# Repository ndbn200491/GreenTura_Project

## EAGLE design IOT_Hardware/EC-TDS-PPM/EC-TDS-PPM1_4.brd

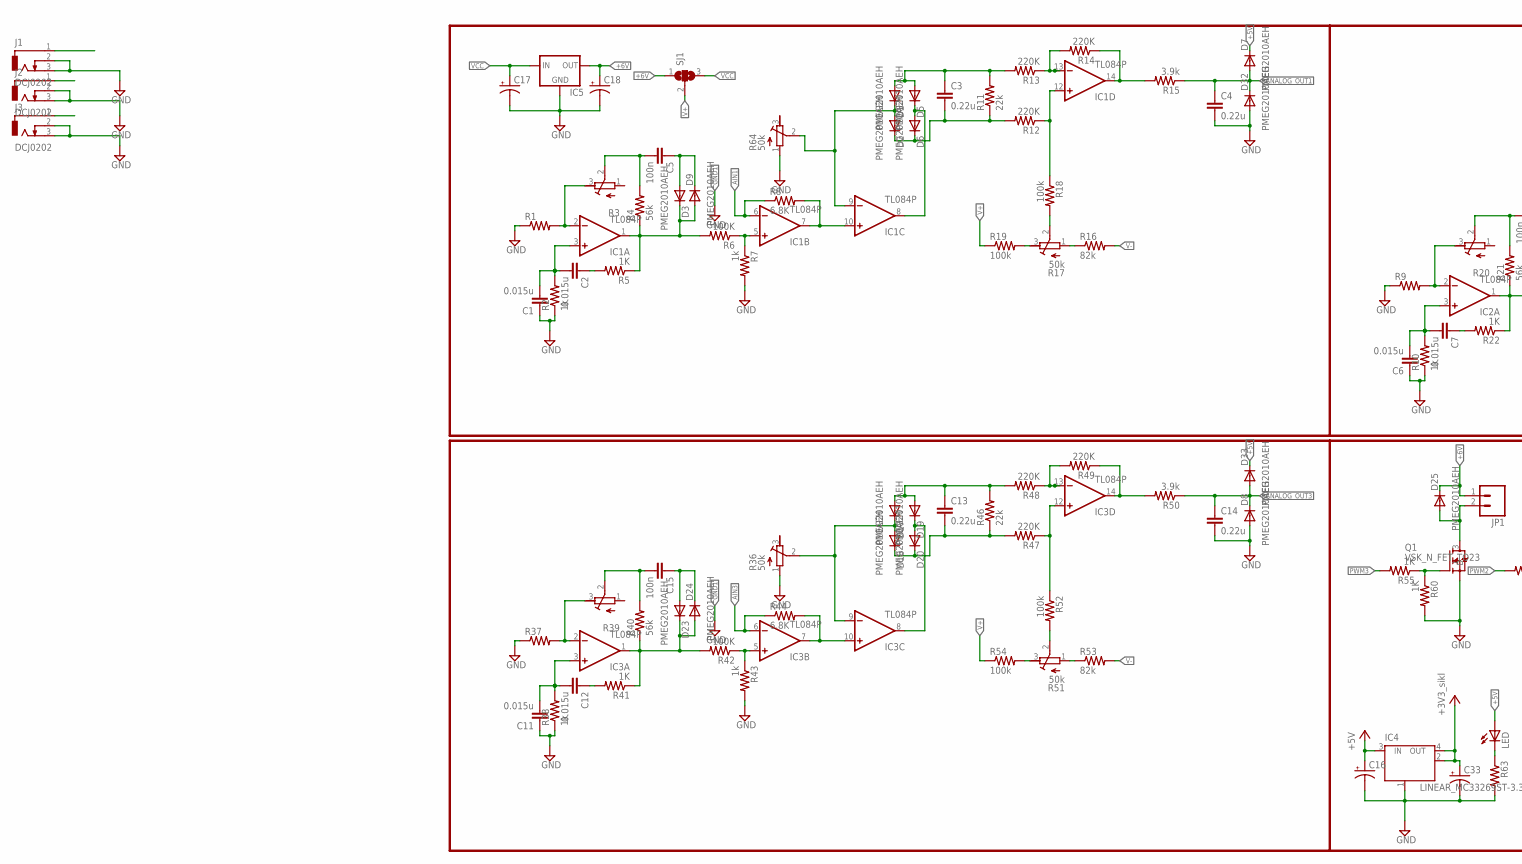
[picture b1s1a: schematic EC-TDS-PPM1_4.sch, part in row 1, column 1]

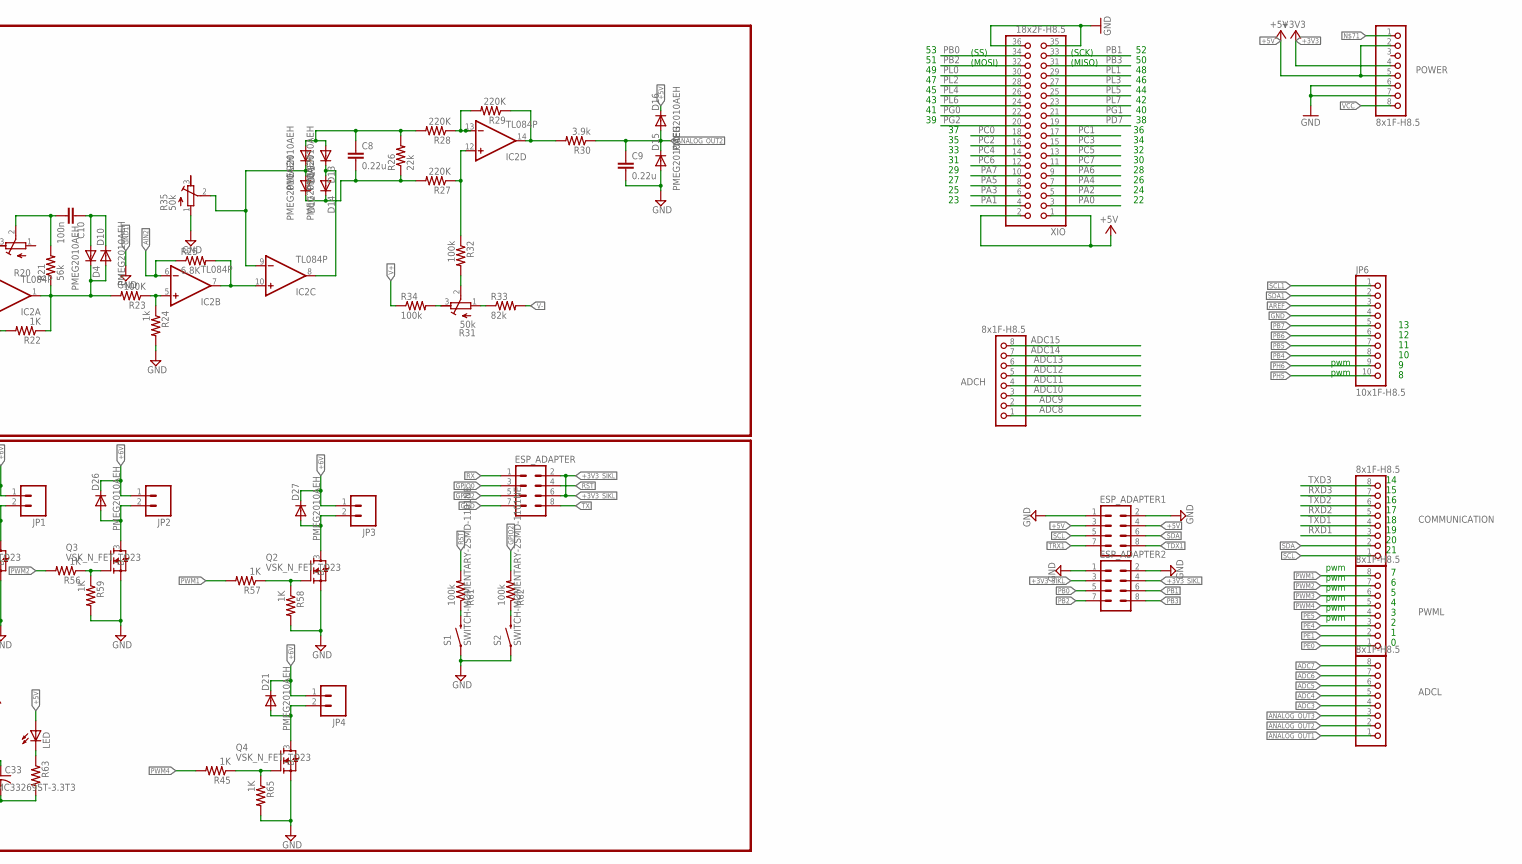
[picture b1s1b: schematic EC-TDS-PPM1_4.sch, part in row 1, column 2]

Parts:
ADCH: 8x1F-H8.5; 1X08
ADCL: 8x1F-H8.5; 1X08
C1, C2, C6, C7, C11, C12: 0.015u; C0603
C3, C4, C8, C9, C13, C14: 0.22u; C0603
C5, C10, C15: 100n; C0603
C16, C17, C18, C33: CPOL-USSMCC; SMC_C
COMMUNICATION: 8x1F-H8.5; 1X08
D1, D2, D3, D4, D5, D6, D7, D8, D9, D10, D11, D12, D13, D14, D15, D16, D17, D18, D19, D20, D21, D23, D24, D25, D26, D27, D32, D33: PMEG2010AEH; SOT123F; PARTNO PMEG2010AEH,115
ESP_ADAPTER, ESP_ADAPTER1, ESP_ADAPTER2: M04X2; 2X4
IC1, IC2, IC3: TL084P; DIL14
IC4: LINEAR_MC33269ST-3.3T3; LINEAR_SOT223
IC5: 78XXS
J1, J2, J3: DCJ0202
JP1, JP2, JP3, JP4: M02PTH; 1X02
JP6: 10x1F-H8.5; 1X10
LED: SPARKFUN_LED0603; SPARKFUN_LED-0603
POWER: 8x1F-H8.5; 1X08
PWML: 8x1F-H8.5; 1X08
Q1, Q2, Q3, Q4: VSK_N_FET_TO23; SOT23
R1, R9, R37: R-US_R0603; R0603
R2, R7, R10, R24, R38, R43: 1k; R0603
R3, R20, R39: R-TRIMM64W; RTRIM64W
R4, R21, R40: 56k; R0603
R5, R22, R41, R45, R55, R56, R57, R58, R59, R60, R65: 1K; R0603
R6, R23, R42: 100K; R0603
R8, R25, R44: 6.8K; R0603
R11, R26, R46: 22k; R0603
R12, R13, R14, R27, R28, R29, R47, R48, R49: 220K; R0603
R15, R30, R50: 3.9k; R0603
R16, R33, R53: 82k; R0603
R17, R31, R35, R36, R51, R64: 50k; RTRIM64W
R18, R19, R32, R34, R52, R54, R61, R62: 100k; R0603
R63: SPARKFUN_RESISTOR0603-RES; SPARKFUN_0603-RES
S1, S2: SWITCH-MOMENTARY-2SMD-1101NE; TACTILE-SWITCH-1101NE
SJ1: SJ2WW; SJ_2W
XIO: 18x2F-H8.5; 2X18

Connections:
+3V3: POWER.4
+3V3_SIKL: C33.+, ESP_ADAPTER.2, ESP_ADAPTER.6, ESP_ADAPTER2.3, ESP_ADAPTER2.4, IC4.2 (OUT), IC4.4 (OUT)
+5V: C16.+, D7.C, D16.C, D33.C, ESP_ADAPTER1.3, ESP_ADAPTER1.4, IC4.3 (IN), LED.A, POWER.2, POWER.5, XIO.1, XIO.2
+6V: C18.+, D21.C, D25.C, D26.C, D27.C, IC5.OUT, JP1.1, JP2.1, JP3.1, JP4.1, SJ1.1
ADC3: ADCL.4
ADC4: ADCL.5
ADC5: ADCL.6
ADC6: ADCL.7
ADC7: ADCL.8
ADC8: ADCH.1
ADC9: ADCH.2
ADC10: ADCH.3
ADC11: ADCH.4
ADC12: ADCH.5
ADC13: ADCH.6
ADC14: ADCH.7
ADC15: ADCH.8
AIN1: IC1.6 (-IN), J1.1, R8.1
AIN2: IC2.6 (-IN), J2.1, R25.1
AIN3: IC3.6 (-IN), J3.1, R44.1
ANALOG_OUT1: ADCL.1, C4.1, D7.A, D32.C, R15.1
ANALOG_OUT2: ADCL.2, C9.1, D15.C, D16.A, R30.1
ANALOG_OUT3: ADCL.3, C14.1, D8.C, D33.A, R50.1
AREF: JP6.3
GND: ESP_ADAPTER.7, JP6.4, POWER.6, POWER.7, XIO.35, XIO.36
GND1: C1.1, C4.2, C6.1, C9.2, C11.1, C14.2, C16.-, C17.-, C18.-, C33.-, D8.A, D15.A, D32.A, ESP_ADAPTER1.1, ESP_ADAPTER1.2, ESP_ADAPTER2.1, ESP_ADAPTER2.2, IC4.1 (GND/ADJ), IC5.GND, J1.2, J1.3, J2.2, J2.3, J3.2, J3.3, Q1.2 (S), Q2.2 (S), Q3.2 (S), Q4.2 (S), R1.1, R2.1, R7.2, R9.1, R10.1, R24.2, R35.1 (A), R36.1 (A), R37.1, R38.1, R43.2, R58.2, R59.2, R60.2, R63.2, R64.1 (A), R65.2, S1.1, S2.1
GPIO0: ESP_ADAPTER.3
GPIO2: ESP_ADAPTER.5, R62.2
unnamed: IC1.2 (-IN), R1.2, R3.3 (E)
unnamed: C2.1, R5.2
unnamed: C1.2, C2.2, IC1.3 (+IN), R2.2
unnamed: IC1.5 (+IN), R6.1, R7.1
unnamed: C5.2, R3.2 (S), R4.2
unnamed: R16.1, R17.1 (A)
unnamed: D3.C, D9.A, IC1.1 (OUT), R4.1, R5.1, R6.2
unnamed: C5.1, D3.A, D9.C
unnamed: IC1.7 (OUT), IC1.10 (+IN), R8.2
unnamed: R17.3 (E), R19.2
unnamed: IC1.13 (-IN), R13.1, R14.2
unnamed: C3.1, D1.A, D5.A, R11.2, R13.2
unnamed: D1.C, D2.A, IC1.9 (-IN), R64.2 (S)
unnamed: C3.2, D2.C, D6.C, R11.1, R12.2
unnamed: D5.C, D6.A, IC1.8 (OUT)
unnamed: IC1.12 (+IN), R12.1, R18.1
unnamed: IC1.14 (OUT), R14.1, R15.2
unnamed: R17.2 (S), R18.2
unnamed: IC2.2 (-IN), R9.2, R20.3 (E)
unnamed: C6.2, C7.2, IC2.3 (+IN), R10.2
unnamed: C10.2, R20.2 (S), R21.2
unnamed: D4.C, D10.A, IC2.1 (OUT), R21.1, R22.1, R23.2
unnamed: C7.1, R22.2
unnamed: IC2.5 (+IN), R23.1, R24.1
unnamed: IC2.7 (OUT), IC2.10 (+IN), R25.2
unnamed: C8.1, D11.A, D13.A, R26.2, R28.2
unnamed: D11.C, D12.A, IC2.9 (-IN), R35.2 (S)
unnamed: C8.2, D12.C, D14.C, R26.1, R27.2
unnamed: D13.C, D14.A, IC2.8 (OUT)
unnamed: IC2.13 (-IN), R28.1, R29.2
unnamed: IC2.12 (+IN), R27.1, R32.1
unnamed: IC2.14 (OUT), R29.1, R30.2
unnamed: C10.1, D4.A, D10.C
unnamed: R31.1 (A), R33.1
unnamed: R31.3 (E), R34.2
unnamed: R31.2 (S), R32.2
unnamed: IC3.2 (-IN), R37.2, R39.3 (E)
unnamed: C11.2, C12.2, IC3.3 (+IN), R38.2
unnamed: C15.2, R39.2 (S), R40.2
unnamed: D23.C, D24.A, IC3.1 (OUT), R40.1, R41.1, R42.2
unnamed: C12.1, R41.2
unnamed: IC3.5 (+IN), R42.1, R43.1
unnamed: IC3.7 (OUT), IC3.10 (+IN), R44.2
unnamed: C13.1, D17.A, D19.A, R46.2, R48.2
unnamed: D17.C, D18.A, IC3.9 (-IN), R36.2 (S)
unnamed: C13.2, D18.C, D20.C, R46.1, R47.2
unnamed: D19.C, D20.A, IC3.8 (OUT)
unnamed: IC3.13 (-IN), R48.1, R49.2
unnamed: IC3.12 (+IN), R47.1, R52.1
unnamed: IC3.14 (OUT), R49.1, R50.2
unnamed: C15.1, D23.A, D24.C
unnamed: R51.1 (A), R53.1
unnamed: R51.3 (E), R54.2
unnamed: R51.2 (S), R52.2
unnamed: D26.A, JP2.2, Q3.3 (D)
unnamed: D27.A, JP3.2, Q2.3 (D)
unnamed: D25.A, JP1.2, Q1.3 (D)
unnamed: Q2.1 (G), R57.1, R58.1
unnamed: Q3.1 (G), R56.1, R59.1
unnamed: D21.A, JP4.2, Q4.3 (D)
unnamed: Q1.1 (G), R55.1, R60.1
unnamed: R61.1, S1.2
unnamed: R62.1, S2.2
unnamed: LED.C, R63.1
unnamed: Q4.1 (G), R45.1, R65.1
PA0: XIO.3
PA1: XIO.4
PA2: XIO.5
PA3: XIO.6
PA4: XIO.7
PA5: XIO.8
PA6: XIO.9
PA7: XIO.10
PB0: ESP_ADAPTER2.5, XIO.34
PB1: ESP_ADAPTER2.6, XIO.33
PB2: ESP_ADAPTER2.7, XIO.32
PB3: ESP_ADAPTER2.8, XIO.31
PB4: JP6.8
PB5: JP6.7
PB6: JP6.6
PB7: JP6.5
PC0: XIO.18
PC1: XIO.17
PC2: XIO.16
PC3: XIO.15
PC4: XIO.14
PC5: XIO.13
PC6: XIO.12
PC7: XIO.11
PD7: XIO.19
PE0: PWML.1
PE1: PWML.2
PE4: PWML.3
PE5: PWML.4
PG0: XIO.22
PG1: XIO.21
PG2: XIO.20
PH5: JP6.10
PH6: JP6.9
PL0: XIO.30
PL1: XIO.29
PL2: XIO.28
PL3: XIO.27
PL4: XIO.26
PL5: XIO.25
PL6: XIO.24
PL7: XIO.23
PWM1: PWML.8, R57.2
PWM2: PWML.7, R56.2
PWM3: PWML.6, R55.2
PWM4: PWML.5, R45.2
RST: ESP_ADAPTER.4, R61.2
RX: ESP_ADAPTER.1
RXD1: COMMUNICATION.3
RXD2: COMMUNICATION.5
RXD3: COMMUNICATION.7
SCL: COMMUNICATION.1, ESP_ADAPTER1.5
SCL1: JP6.1
SDA: COMMUNICATION.2, ESP_ADAPTER1.6
SDA1: JP6.2
TDX1: ESP_ADAPTER1.8
TRX1: ESP_ADAPTER1.7
TX: ESP_ADAPTER.8
TXD1: COMMUNICATION.4
TXD2: COMMUNICATION.6
TXD3: COMMUNICATION.8
V+: IC1.4 (V+), IC2.4 (V+), IC3.4 (V+), R19.1, R34.1, R54.1, SJ1.2
V-: IC1.11 (V-), IC2.11 (V-), IC3.11 (V-), R16.2, R33.2, R53.2
VCC: C17.+, IC5.IN, POWER.8, SJ1.3

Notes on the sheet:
(SS)
(MOSI)
(SCK)
(MISO)
pwm

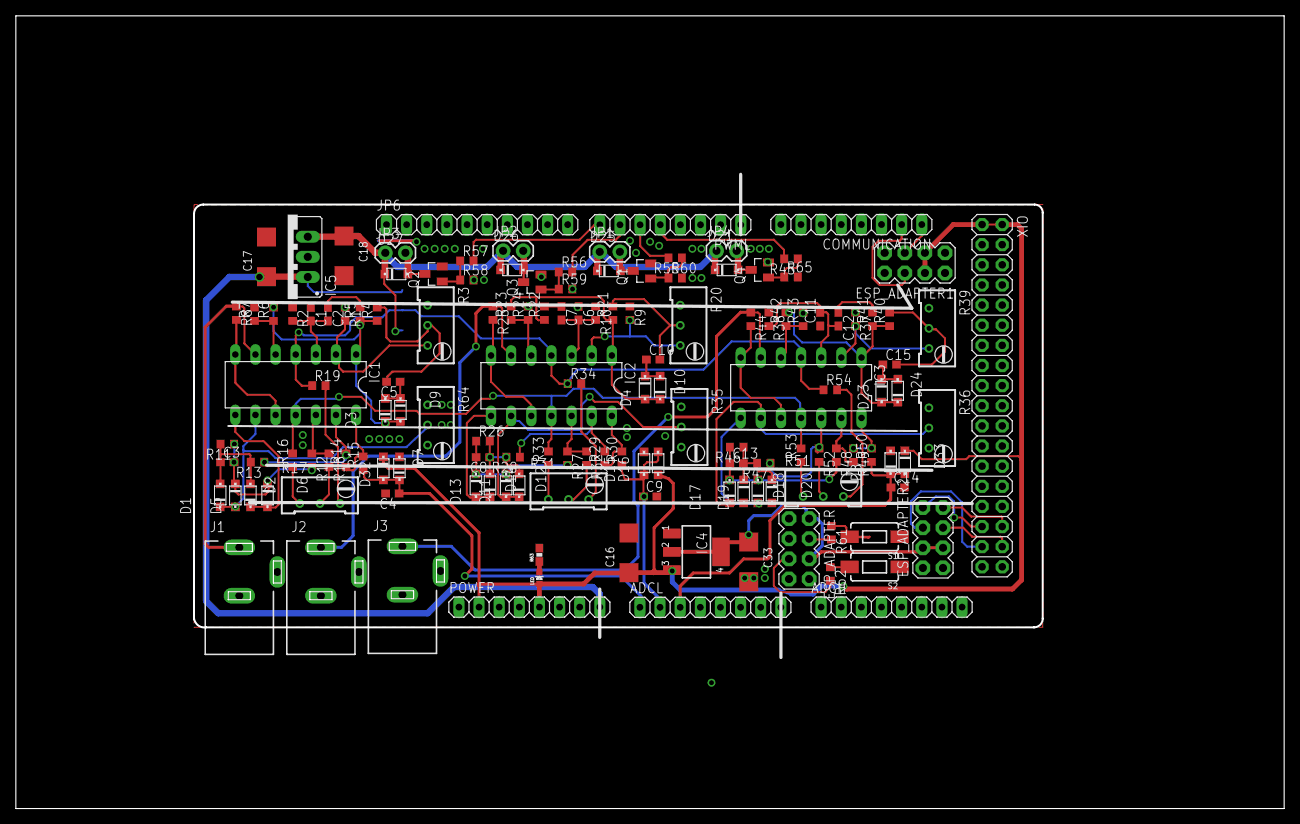
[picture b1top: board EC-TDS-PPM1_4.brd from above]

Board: 2 copper layers, 159.7 x 99.7 mm, 142 parts (1 on the bottom side), 91 nets.

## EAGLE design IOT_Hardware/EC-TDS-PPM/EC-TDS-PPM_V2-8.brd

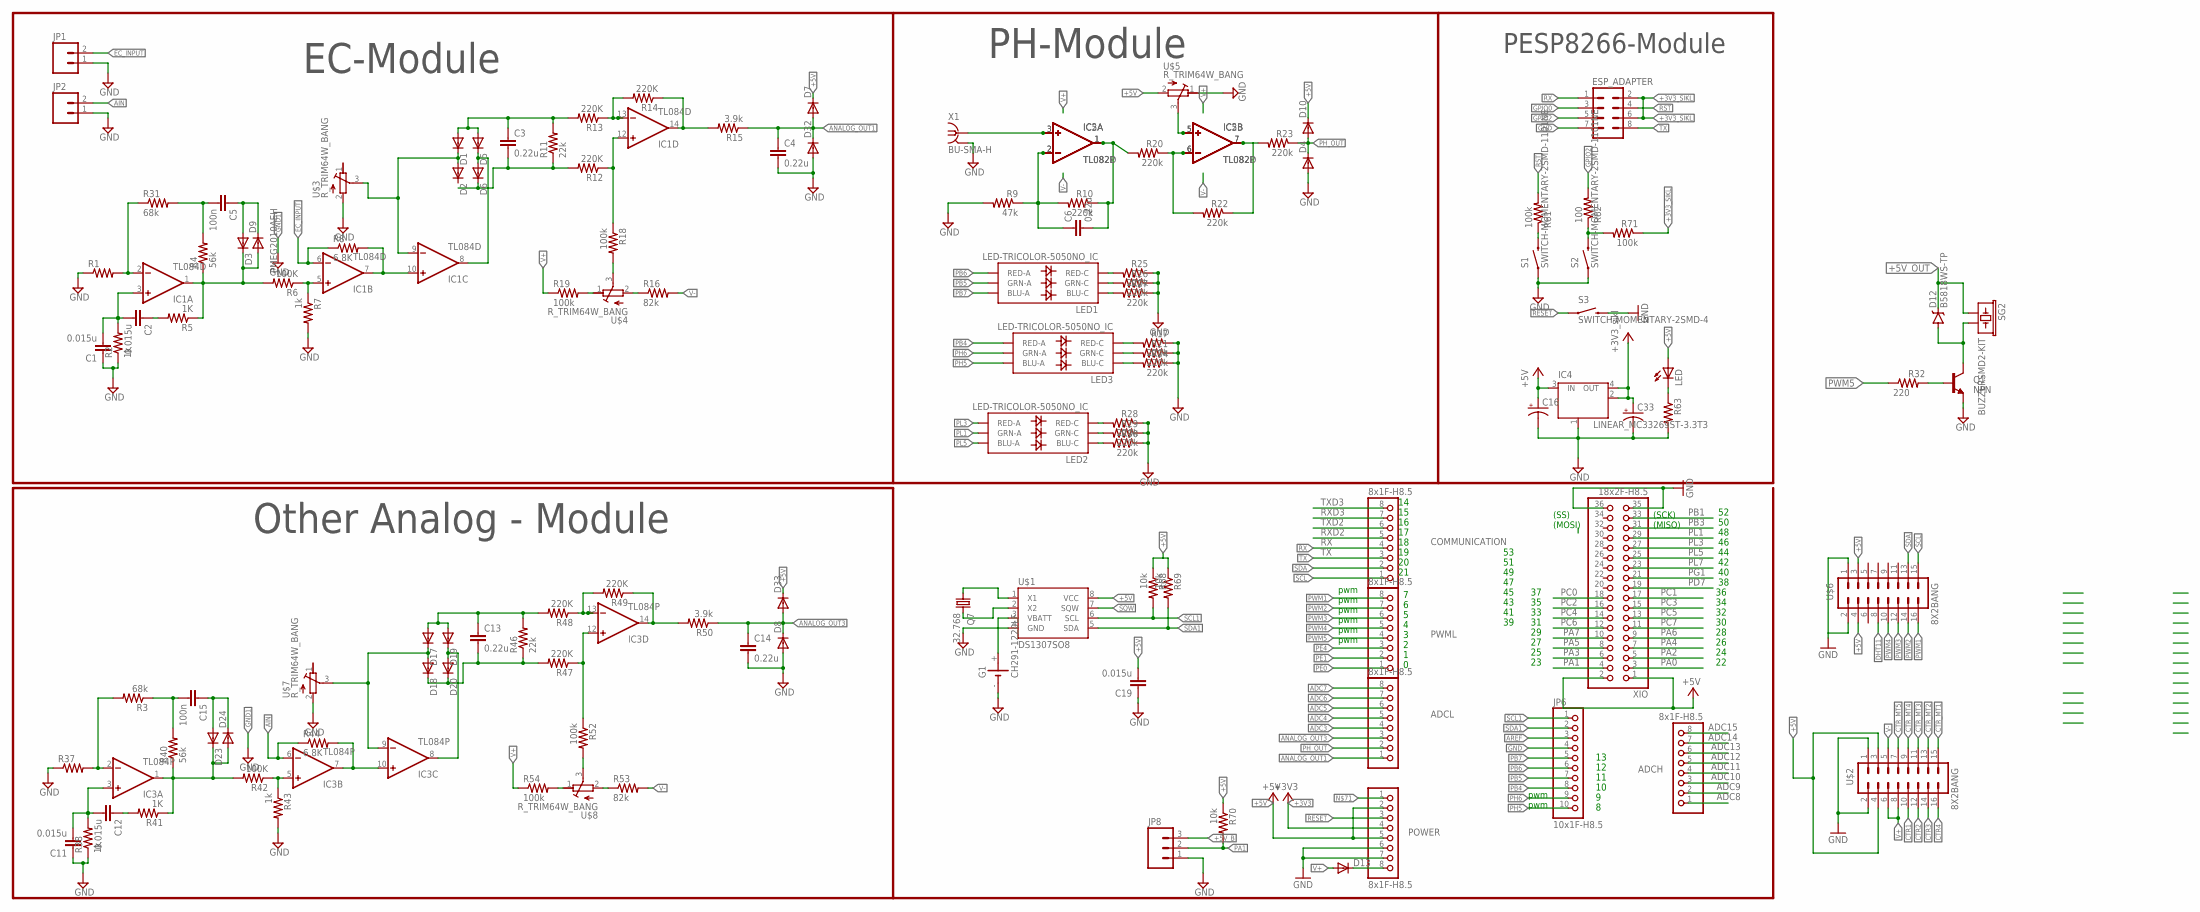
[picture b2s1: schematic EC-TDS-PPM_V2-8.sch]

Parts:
ADCH: 8x1F-H8.5; 1X08
ADCL: 8x1F-H8.5; 1X08
C1, C2, C11, C12, C19: 0.015u; C0603
C3, C4, C6, C13, C14: 0.22u; C0603
C5, C15: 100n; C0603
C16, C33: CPOL-USSMCC; SMC_C
COMMUNICATION: 8x1F-H8.5; 1X08
D1, D2, D3, D4, D5, D6, D7, D8, D9, D10, D13, D17, D18, D19, D20, D23, D24, D32, D33: PMEG2010AEH; SOT123F; PARTNO PMEG2010AEH,115
D12: B5818WS-TP; SOD-323; PARTNO BAT20JFILM
ESP_ADAPTER: M04X2; 2X4
G1: CH291-1220LF
IC1: TL084D; SO14
IC2: TL082P; DIL08
IC3: TL084P; DIL14
IC4: LINEAR_MC33269ST-3.3T3; LINEAR_SOT223
IC5: TL082D; SO08
JP1, JP2: M025MM; SCREWTERMINAL-5MM-2
JP6: 10x1F-H8.5; 1X10
JP8: M03PTH; 1X03
LED: SPARKFUN_LED0603; SPARKFUN_LED-0603
LED1, LED2, LED3: LED-TRICOLOR-5050NO_IC; LED-TRICOLOR-5050
POWER: 8x1F-H8.5; 1X08
PWML: 8x1F-H8.5; 1X08
Q1: NPN; SOT23-3; PARTNO 2SD1048-6-TB-E
Q7: 32.768; TC38H
R1, R37: R-US_R0603; R0603
R2, R7, R38, R43: 1k; R0603
R3, R31: 68k; R0603
R4, R40: 56k; R0603
R5, R41: 1K; R0603
R6, R42: 100K; R0603
R8, R44: 6.8K; R0603
R9: 47k; R0603
R10, R17, R20, R21, R22, R23, R24, R25, R26, R27, R28, R29, R30: 220k; R0603
R11, R46: 22k; R0603
R12, R13, R14, R47, R48, R49: 220K; R0603
R15, R50: 3.9k; R0603
R16, R53: 82k; R0603
R18, R19, R52, R54, R61, R71: 100k; R0603
R32: 220; 0603-RES; PARTNO RT0402DRE079K09L
R62: 100; R0603
R63: SPARKFUN_RESISTOR0603-RES; SPARKFUN_0603-RES
R68, R69, R70: 10k; R0603
S1, S2: SWITCH-MOMENTARY-2SMD-1101NE; TACTILE-SWITCH-1101NE
S3: SWITCH-MOMENTARY-2SMD-4; TACTILE_SWITCH_TALL
SG2: BUZZERSMD2-KIT; BUZZER-CCV-KIT
U$1: DS1307SO8; SO08
U$2, U$6: 8X2BANG
U$3, U$4, U$5, U$7, U$8: R_TRIM64W_BANG; RTRIM64W_BANG
X1: BU-SMA-H
XIO: 18x2F-H8.5; 2X18

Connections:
+3V3: POWER.4
+3V3_SIKL: C33.+, ESP_ADAPTER.2, ESP_ADAPTER.6, IC4.2 (OUT), IC4.4 (OUT), R71.1
+5V: C16.+, C19.2, D7.C, D10.C, D33.C, IC4.3 (IN), LED.A, POWER.2, POWER.5, R68.1, R69.1, R70.1, U$1.8 (VCC), U$2.3, U$2.4, U$5.2 (E), U$6.3, U$6.4
+5V_B: JP8.3, XIO.1, XIO.2
+5V_OUT: D12.C, SG2.+ (1)
ADC3: ADCL.4
ADC4: ADCL.5
ADC5: ADCL.6
ADC6: ADCL.7
ADC7: ADCL.8
ADC8: ADCH.1
ADC9: ADCH.2
ADC10: ADCH.3
ADC11: ADCH.4
ADC12: ADCH.5
ADC13: ADCH.6
ADC14: ADCH.7
ADC15: ADCH.8
AIN: IC3.6 (-IN), JP2.2, R44.1
ANALOG_OUT1: ADCL.1, C4.1, D7.A, D32.C, R15.1
ANALOG_OUT3: ADCL.3, C14.1, D8.C, D33.A, R50.1
AREF: JP6.3
CTR1: U$2.10
CTR2: U$2.12
CTR3: U$2.14
CTR4: U$2.16
CTR_MT1: U$2.15
CTR_MT2: U$2.13
CTR_MT3: U$2.11
CTR_MT4: U$2.9
CTR_MT5: U$2.7
DHT11: U$6.8
EC_INPUT: IC1.6 (-IN), JP1.2, R8.1
GND: C1.1, C4.2, C11.1, C14.2, C16.-, C19.1, C33.-, D4.A, D8.A, D32.A, ESP_ADAPTER.7, G1.-, IC4.1 (GND/ADJ), JP1.1, JP2.1, JP6.4, JP8.1, POWER.6, POWER.7, Q1.2 (E), R1.1, R2.1, R7.2, R9.2, R17.1, R21.1, R24.1, R25.1, R26.1, R27.1, R28.1, R29.1, R30.1, R37.1, R38.1, R43.2, R63.2, S1.1, S2.1, S3.B2 (2), U$1.4 (GND), U$2.1, U$2.2, U$3.2 (E), U$6.1, U$6.2, U$7.2 (E), X1.2, X1.3 (2), X1.4 (2), X1.5 (2), XIO.35, XIO.36
GND1: U$5.1 (A)
GPIO0: ESP_ADAPTER.3
GPIO2: ESP_ADAPTER.5, R62.2
unnamed: IC1.2 (-IN), R1.2, R31.1
unnamed: C2.1, R5.2
unnamed: C1.2, C2.2, IC1.3 (+IN), R2.2
unnamed: IC1.5 (+IN), R6.1, R7.1
unnamed: C5.2, R4.2, R31.2
unnamed: R16.1, U$4.2 (E)
unnamed: D3.C, D9.A, IC1.1 (OUT), R4.1, R5.1, R6.2
unnamed: C5.1, D3.A, D9.C
unnamed: IC1.7 (OUT), IC1.10 (+IN), R8.2
unnamed: R19.2, U$4.1 (A)
unnamed: IC1.13 (-IN), R13.1, R14.2
unnamed: C3.1, D1.A, D5.A, R11.2, R13.2
unnamed: D1.C, D2.A, IC1.9 (-IN), U$3.3 (S)
unnamed: C3.2, D6.C, R11.1, R12.2
unnamed: D5.C, D6.A, IC1.8 (OUT)
unnamed: IC1.12 (+IN), R12.1, R18.1
unnamed: IC1.14 (OUT), R14.1, R15.2
unnamed: R18.2, U$4.3 (S)
unnamed: IC2.5 (+IN), IC5.5 (+IN), U$5.3 (S)
unnamed: IC2.6 (-IN), IC5.6 (-IN), R20.1, R22.2
unnamed: C6.1, IC2.2 (-IN), IC5.2 (-IN), R9.1, R10.2
unnamed: C6.2, IC2.1 (OUT), IC5.1 (OUT), R10.1, R20.2
unnamed: IC2.7 (OUT), IC5.7 (OUT), R22.1, R23.2
unnamed: IC2.3 (+IN), IC5.3 (+IN), X1.1
unnamed: LED3.5 (RED-C), R17.2
unnamed: LED3.6 (GRN-C), R21.2
unnamed: LED2.5 (RED-C), R28.2
unnamed: LED2.6 (GRN-C), R29.2
unnamed: LED2.4 (BLU-C), R30.2
unnamed: LED3.4 (BLU-C), R24.2
unnamed: LED1.5 (RED-C), R25.2
unnamed: LED1.6 (GRN-C), R26.2
unnamed: LED1.4 (BLU-C), R27.2
unnamed: Q1.1 (B), R32.2
unnamed: D12.A, Q1.3 (C), SG2.- (2)
unnamed: IC3.2 (-IN), R3.2, R37.2
unnamed: C11.2, C12.2, IC3.3 (+IN), R38.2
unnamed: C15.2, R3.1, R40.2
unnamed: D23.C, D24.A, IC3.1 (OUT), R40.1, R41.1, R42.2
unnamed: C12.1, R41.2
unnamed: IC3.5 (+IN), R42.1, R43.1
unnamed: IC3.7 (OUT), IC3.10 (+IN), R44.2
unnamed: C13.1, D17.A, D19.A, R46.2, R48.2
unnamed: D17.C, D18.A, IC3.9 (-IN), U$7.3 (S)
unnamed: C13.2, D18.C, D20.C, R46.1, R47.2
unnamed: D19.C, D20.A, IC3.8 (OUT)
unnamed: IC3.13 (-IN), R48.1, R49.2
unnamed: IC3.12 (+IN), R47.1, R52.1
unnamed: IC3.14 (OUT), R49.1, R50.2
unnamed: C15.1, D23.A, D24.C
unnamed: R53.1, U$8.2 (E)
unnamed: R54.2, U$8.1 (A)
unnamed: R52.2, U$8.3 (S)
unnamed: D13.C, POWER.8
unnamed: R61.1, S1.2
unnamed: R62.1, R71.2, S2.2
unnamed: LED.C, R63.1
unnamed: Q7.1, U$1.1 (X1)
unnamed: Q7.2, U$1.2 (X2)
unnamed: G1.+, U$1.3 (VBATT)
PA0: XIO.3
PA1: JP8.2, R70.2, XIO.4
PA2: XIO.5
PA3: XIO.6
PA4: XIO.7
PA5: XIO.8
PA6: XIO.9
PA7: XIO.10
PB1: XIO.33
PB3: XIO.31
PB4: JP6.8, LED3.2 (RED-A)
PB5: JP6.7, LED1.1 (GRN-A)
PB6: JP6.6, LED1.2 (RED-A)
PB7: JP6.5, LED1.3 (BLU-A)
PC0: XIO.18
PC1: XIO.17
PC2: XIO.16
PC3: XIO.15
PC4: XIO.14
PC5: XIO.13
PC6: XIO.12
PC7: XIO.11
PD7: XIO.19
PE0: PWML.1
PE1: PWML.2
PE4: PWML.3
PG1: XIO.21
PH5: JP6.10, LED3.3 (BLU-A)
PH6: JP6.9, LED3.1 (GRN-A)
PH_OUT: ADCL.2, D4.C, D10.A, R23.1
PL1: LED2.1 (GRN-A), XIO.29
PL3: LED2.2 (RED-A), XIO.27
PL5: LED2.3 (BLU-A), XIO.25
PL7: XIO.23
PWM1: PWML.8, U$6.16
PWM2: PWML.7, U$6.14
PWM3: PWML.6, U$6.12
PWM4: PWML.5, U$6.10
PWM5: PWML.4, R32.1
RESET: POWER.3, S3.A2 (1)
RST: ESP_ADAPTER.4, R61.2
RX: COMMUNICATION.4, ESP_ADAPTER.1
RXD2: COMMUNICATION.5
RXD3: COMMUNICATION.7
SCL: COMMUNICATION.1, U$6.15
SCL1: JP6.1, R68.2, U$1.6 (SCL)
SDA: COMMUNICATION.2, U$6.13
SDA1: JP6.2, R69.2, U$1.5 (SDA)
SQW: U$1.7 (SQW)
TX: COMMUNICATION.3, ESP_ADAPTER.8
TXD2: COMMUNICATION.6
TXD3: COMMUNICATION.8
V+: D13.A, IC1.4 (V+), IC2.8 (V+), IC3.4 (V+), IC5.8 (V+), R19.1, R54.1, U$2.6, U$2.8
V-: IC1.11 (V-), IC2.4 (V-), IC3.11 (V-), IC5.4 (V-), R16.2, R53.2, U$2.5

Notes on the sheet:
(SS)
(MOSI)
(SCK)
(MISO)
pwm
EC-Module
PH-Module
Other Analog - Module
PESP8266-Module

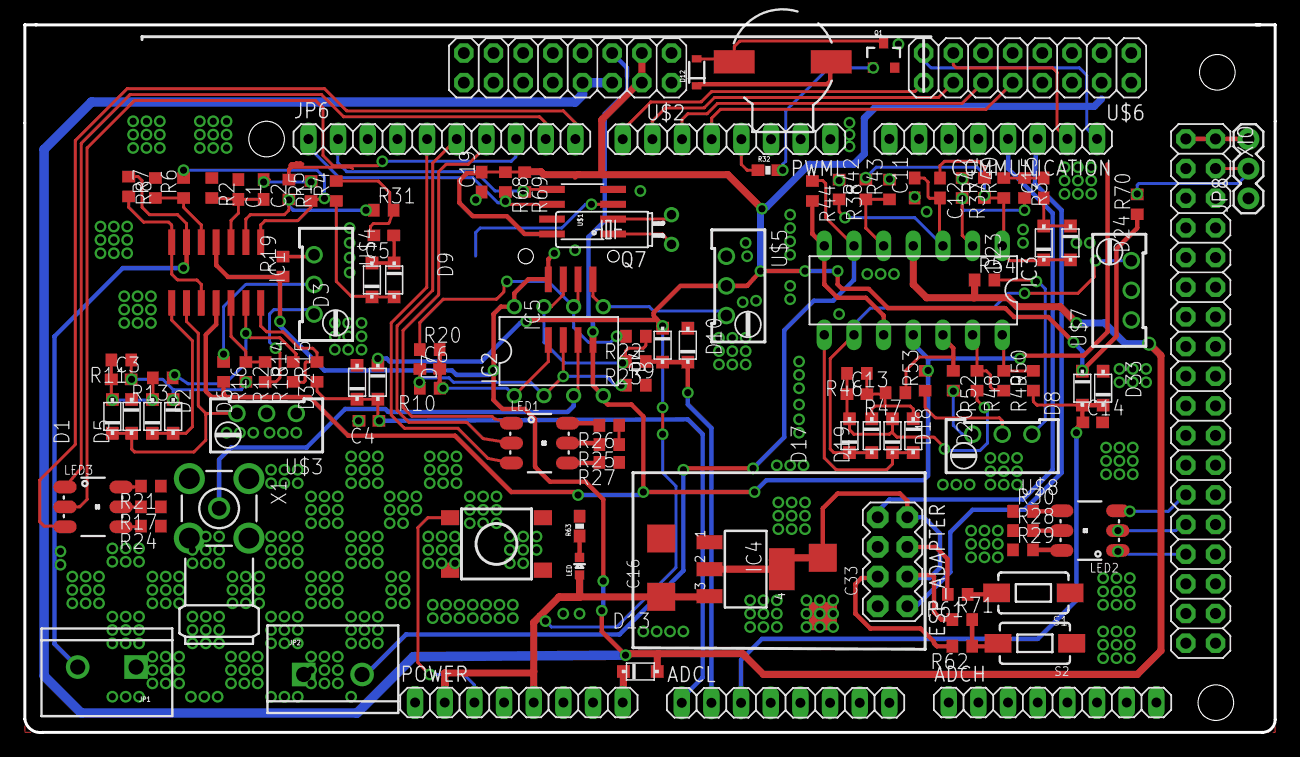
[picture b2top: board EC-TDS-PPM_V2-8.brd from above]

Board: 2 copper layers, 107.1 x 60.6 mm, 124 parts (1 on the bottom side), 96 nets.

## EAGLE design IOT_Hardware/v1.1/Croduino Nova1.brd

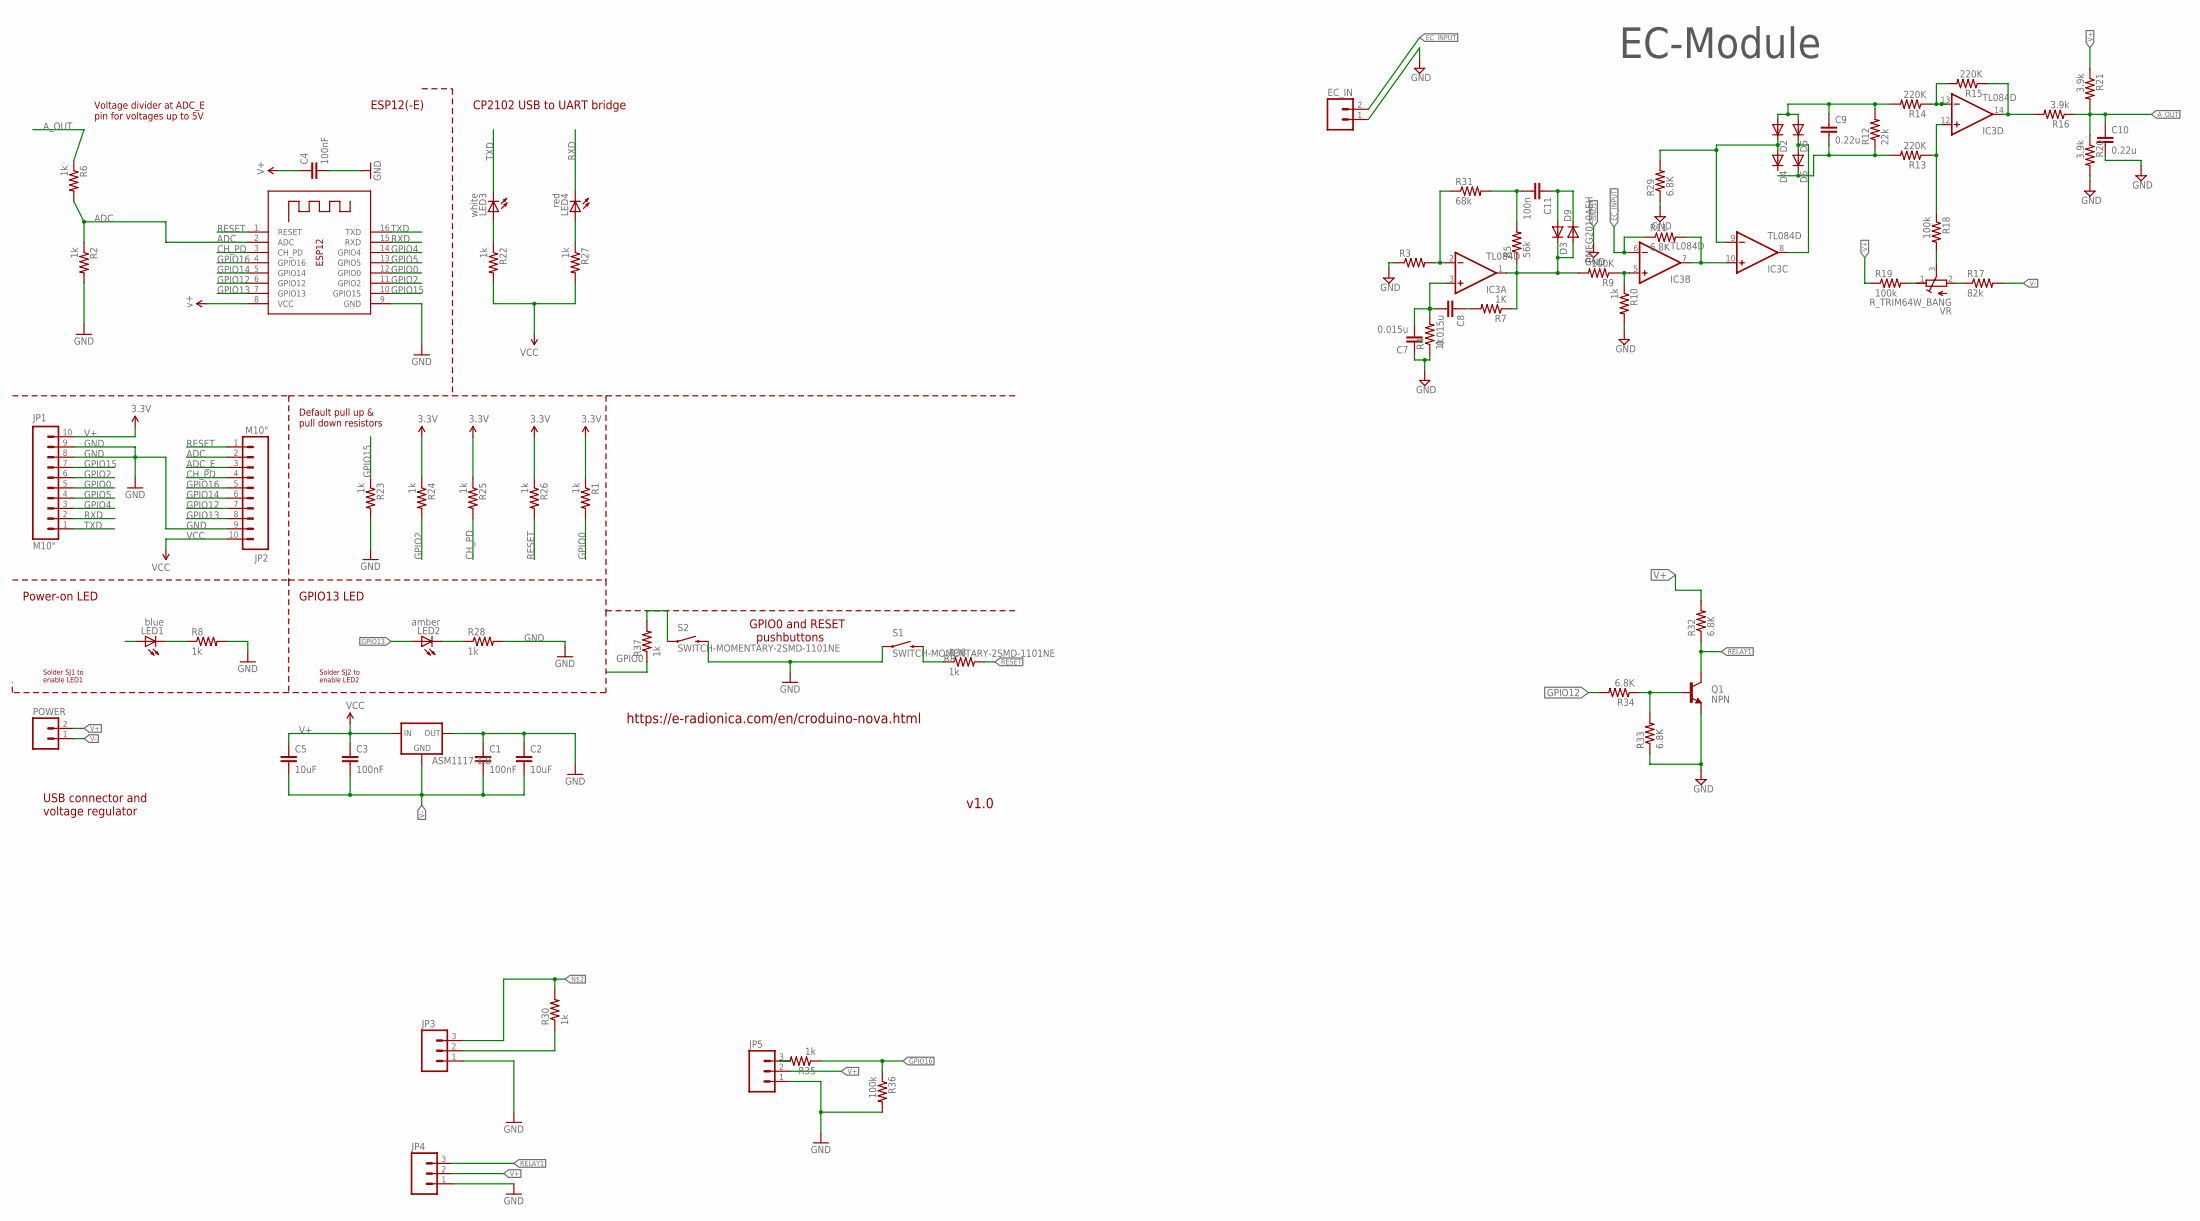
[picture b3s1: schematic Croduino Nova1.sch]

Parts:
ASM1117-1.8: AMS1117-3.3; SOT223
C1, C3, C4: 100nF; 0603-CAP
C2, C5: 10uF; 1206
C7, C8: 0.015u; C0603
C9, C10: 0.22u; C0603
C11: 100n; C0603
D2, D3, D4, D5, D6, D9: PMEG2010AEH; SOT123F; PARTNO PMEG2010AEH,115
EC_IN: M025MM; SCREWTERMINAL-5MM-2
IC3: TL084D; SO14
JP1, JP2: M10"; 1X10
JP3, JP4, JP5: M03PTH; 1X03
LED1: blue; CHIP-LED0603
LED2: amber; CHIPLED_0603
LED3: white; CHIP-LED0805
LED4: red; CHIP-LED0805
POWER: M02LOCK_LONGPADS; 1X02_LOCK_LONGPADS
Q1: NPN; SOT23-3; PARTNO 2SD1048-6-TB-E
R1, R2, R4, R6, R8, R10, R22, R23, R24, R25, R26, R27, R28, R30, R35, R37, R38: 1k; R0603
R3: R-US_R0603; R0603
R5: 56k; R0603
R7: 1K; R0603
R9: 100K; R0603
R11, R29, R32, R33, R34: 6.8K; R0603
R12: 22k; R0603
R13, R14, R15: 220K; R0603
R16, R20, R21: 3.9k; R0603
R17: 82k; R0603
R18, R19, R36: 100k; R0603
R31: 68k; R0603
S1, S2: SWITCH-MOMENTARY-2SMD-1101NE; TACTILE-SWITCH-1101NE
VR: R_TRIM64W_BANG; RTRIM64W_BANG
X1: ESP8266-12; ESP-12

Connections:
ADC: JP2.2, R2.1, R6.2, X1.2 (ADC)
ADC_E: JP2.3
A_OUT: C10.1, R6.1, R16.1, R20.1, R21.2
CH_PD: JP2.4, R25.2, X1.3 (CH_PD)
EC_INPUT: EC_IN.2, IC3.6 (-IN), R11.1
ERFS: Q1.1 (B), R33.2, R34.1
GND: ASM1117-1.8.4 (OUT), C1.1, C2.1, C4.2, C7.1, C10.2, EC_IN.1, JP1.8, JP1.9, JP2.9, JP3.1, JP4.1, JP5.1, Q1.2 (E), R2.2, R3.1, R4.1, R8.2, R10.2, R23.2, R28.2, R29.1, R33.1, R36.2, S1.1, S2.2, X1.9 (GND)
GND1: R20.2
GPIO0: JP1.5, R1.2, R37.1, X1.12 (GPIO0)
GPIO2: JP1.6, R24.2, X1.11 (GPIO2)
GPIO4: JP1.3, X1.14 (GPIO4)
GPIO5: JP1.4, X1.13 (GPIO5)
GPIO12: JP2.7, R34.2, X1.6 (GPIO12)
GPIO13: JP2.8, LED2.A, X1.7 (GPIO13)
GPIO14: JP2.6, X1.5 (GPIO14)
GPIO15: JP1.7, R23.1, X1.10 (GPIO15)
GPIO16: JP2.5, R35.1, R36.1, X1.4 (GPIO16)
unnamed: LED3.A, R22.1
unnamed: JP3.3, R30.2
unnamed: LED1.C, R8.1
unnamed: LED4.A, R27.1
unnamed: IC3.2 (-IN), R3.2, R31.1
unnamed: JP5.3, R35.2
unnamed: LED2.C, R28.1
unnamed: C7.2, C8.2, IC3.3 (+IN), R4.2
unnamed: C11.2, R5.2, R31.2
unnamed: R37.2, S2.1
unnamed: D3.C, D9.A, IC3.1 (OUT), R5.1, R7.1, R9.2
unnamed: C8.1, R7.2
unnamed: IC3.5 (+IN), R9.1, R10.1
unnamed: IC3.7 (OUT), IC3.10 (+IN), R11.2
unnamed: C9.1, D2.A, D5.A, R12.2, R14.2
unnamed: D2.C, D4.A, IC3.9 (-IN), R29.2
unnamed: C9.2, D6.C, R12.1, R13.2
unnamed: D5.C, D6.A, IC3.8 (OUT)
unnamed: IC3.13 (-IN), R14.1, R15.2
unnamed: IC3.12 (+IN), R13.1, R18.1
unnamed: IC3.14 (OUT), R15.1, R16.2
unnamed: C11.1, D3.A, D9.C
unnamed: R17.1, VR.2 (E)
unnamed: R19.2, VR.1 (A)
unnamed: R18.2, VR.3 (S)
RELAY1: JP4.3, Q1.3 (C), R32.1
RESET: JP2.1, R26.2, R38.2, X1.1 (RESET)
RR: R38.1, S1.2
RXD: JP1.2, LED4.C, X1.15 (RXD)
TXD: JP1.1, LED3.C, X1.16 (TXD)
V+: ASM1117-1.8.3 (IN), C3.1, C4.1, C5.1, IC3.4 (V+), JP1.10, JP3.2, JP4.2, JP5.2, LED1.A, POWER.2, R1.1, R19.1, R21.1, R24.1, R25.1, R26.1, R30.1, R32.2, X1.8 (VCC)
V-: ASM1117-1.8.1 (ADJ), C1.2, C2.2, C3.2, C5.2, IC3.11 (V-), POWER.1, R17.2
VCC: JP2.10, R22.2, R27.2

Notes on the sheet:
USB connector and voltage regulator
Power-on LED
GPIO13 LED
Solder SJ1 to enable LED1
Solder SJ2 to enable LED2
ESP12(-E)
CP2102 USB to UART bridge
Voltage divider at ADC_E pin for voltages up to 5V
Default pull up & pull down resistors
GPIO0 and RESET pushbuttons
https://e-radionica.com/en/croduino-nova.html
v1.0
EC-Module

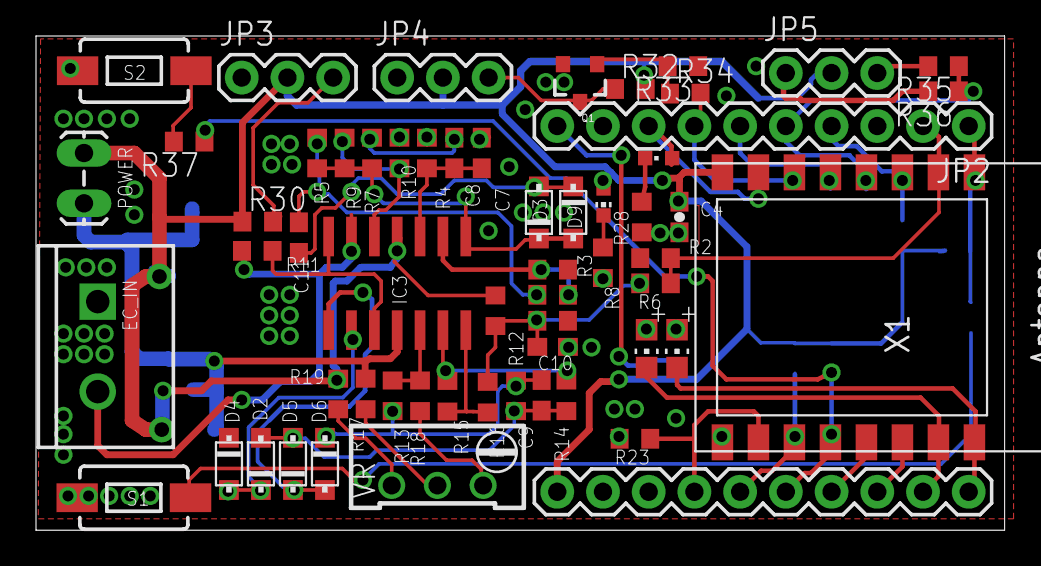
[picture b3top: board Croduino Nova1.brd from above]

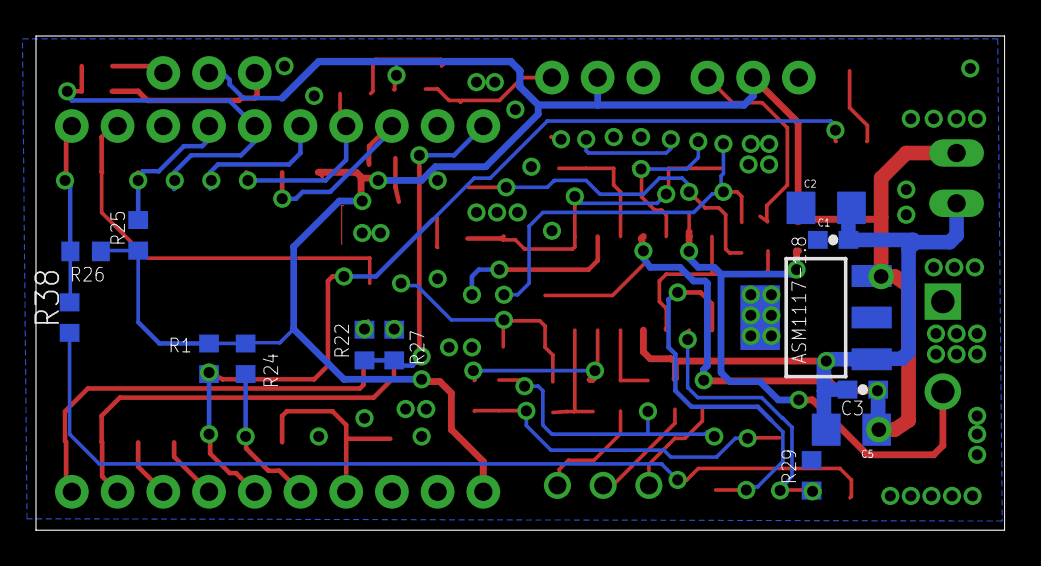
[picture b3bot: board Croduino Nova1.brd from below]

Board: 2 copper layers, 53.8 x 27.5 mm, 75 parts (13 on the bottom side), 48 nets.

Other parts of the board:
U$2: CRODUINO_NOVA
U$3: NOVI_LOGO-4MM
U$4: OSH3MM

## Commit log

2016-10-25 New Commit Signed-off-by: BangNguyen <ndbn200491@gmail.com>
2016-10-26 GreenTool_v4_login
2016-10-26 -GreenTool_new Signed-off-by: BangNguyen <ndbn200491@gmail.com>
2016-10-26 --Show setting page Signed-off-by: BangNguyen <ndbn200491@gmail.com>

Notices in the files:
parts and their libraries:
SparkFun-Connectors: Licensing: Creative Commons ShareAlike 4.0 International - https://creativecommons.org/licenses/by-sa/4.0
SparkFun: Licensing: CC v3.0 Share-Alike You are welcome to use this library for commercial purposes.
